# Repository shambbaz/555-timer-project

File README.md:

# 555 Timer Project

### Piirikaavio

### PCB-suunnittelu

Tämä on harjoitustyö, jossa suunniteltiin pintaliitoskomponenteilla toteutettava 555-ajastinpiiri.

## Projektin sisältö
- **Piirikaavio (schematic):** Näyttää komponenttien väliset kytkennät.
- **Piirikuva (layout):** Sisältää komponenttien sijoittelun ja johdotuksen.
- **DRC-raportti:** Varmistaa suunnittelun virheettömyyden.

## Kuinka avata projekti
1. Lataa kaikki tiedostot.
2. Avaa KiCad-ohjelmistossa `555-timer-project.pro`.

## Oppimispisteet
- KiCad-ohjelmiston käyttö.
- Piirilevyjen suunnittelun perusteet.

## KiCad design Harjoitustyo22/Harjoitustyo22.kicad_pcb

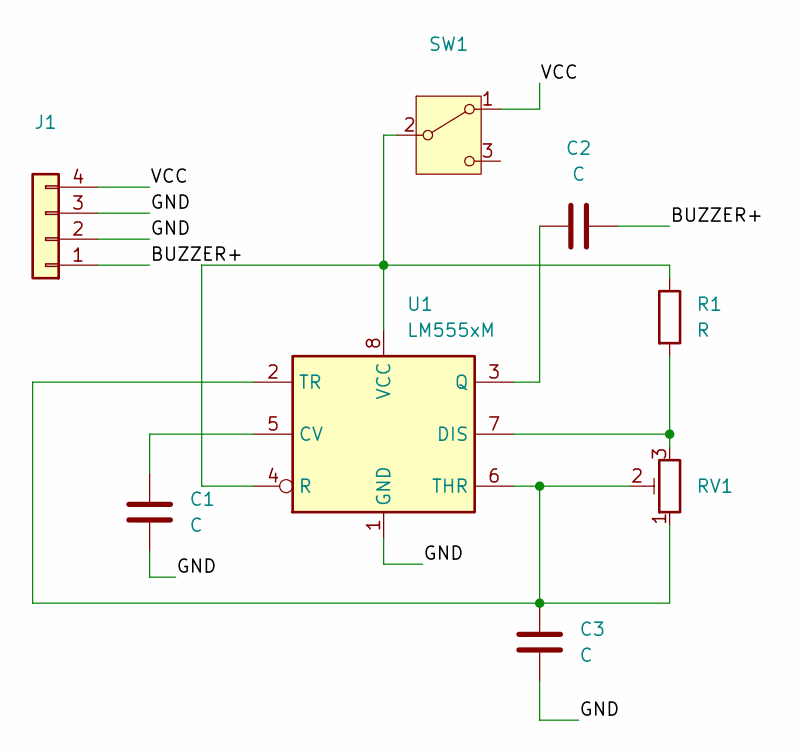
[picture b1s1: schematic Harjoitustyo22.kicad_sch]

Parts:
C1, C2, C3: C; C_1206_3216Metric
J1: PinHeader_1x04_P2.54mm_Horizontal
R1: R; R_1206_3216Metric
RV1: Potentiometer_Bourns_TC33X_Vertical
SW1: SW_SPDT_PCM12
U1: LM555xM; SOIC-8_3.9x4.9mm_P1.27mm

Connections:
/BUZZER+: C2.2, J1.1
/GND: C1.2, C3.2, J1.2, J1.3, U1.1 (GND)
/VCC: J1.4, SW1.1 (A)
unnamed: R1.1, SW1.2 (B), U1.4 (R), U1.8 (VCC)
unnamed: C1.1, U1.5 (CV)
unnamed: R1.2, RV1.3, U1.7 (DIS)
unnamed: C2.1, U1.3 (Q)
unnamed: C3.1, RV1.1, RV1.2, U1.2 (TR), U1.6 (THR)

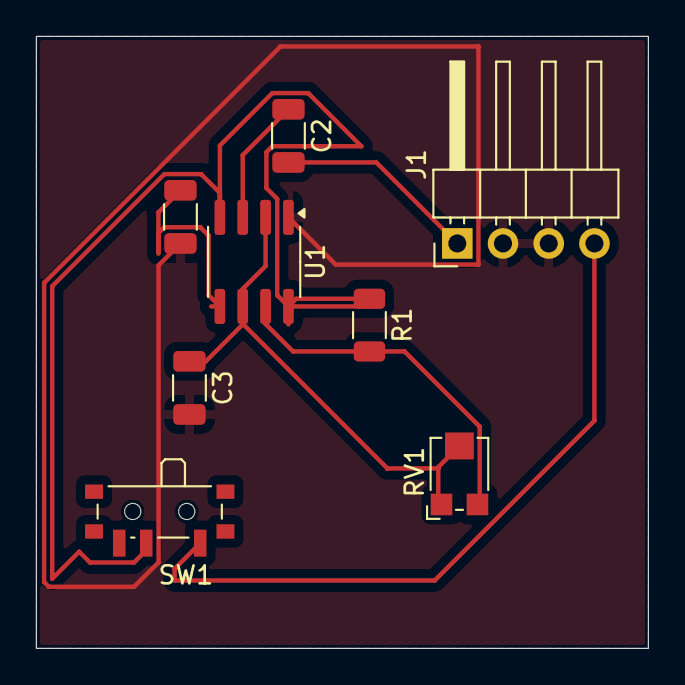
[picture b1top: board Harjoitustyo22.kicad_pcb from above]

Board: 2 copper layers, 34.0 x 34.0 mm, 8 parts (0 on the bottom side), 8 nets.

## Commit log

2024-11-29 Create 555timer-project
